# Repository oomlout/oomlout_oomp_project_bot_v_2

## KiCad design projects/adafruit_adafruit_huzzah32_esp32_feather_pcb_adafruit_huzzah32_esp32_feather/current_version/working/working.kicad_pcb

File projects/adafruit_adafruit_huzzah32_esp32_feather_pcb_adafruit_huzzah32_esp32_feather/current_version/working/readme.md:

# adafruit_huzzah32_esp32_feather_pcb
 
## summary 
* id: adafruit_adafruit_huzzah32_esp32_feather_pcb_adafruit_huzzah32_esp32_feather
* user: adafruit
* name: adafruit_huzzah32_esp32_feather_pcb
* board: adafruit_huzzah32_esp32_feather
* repo: https://github.com/adafruit/Adafruit-HUZZAH32-ESP32-Feather-PCB

* src_file_repo_sch: 
* src_file_repo_sch_link: https://github.com/adafruit/Adafruit-HUZZAH32-ESP32-Feather-PCB/tree/master/
* full details link: https://github.com/oomlout/oomlout_oomp_project_bot_v_2/tree/main/projects/adafruit_adafruit_huzzah32_esp32_feather_pcb_adafruit_huzzah32_esp32_feather/current_version/working  

## schematic  
  
[schematic (pdf)](working_schematic.pdf) 

## pcb  

[board (pdf)](working.pdf)  

## working_bom
| Id | Designator | Footprint | Quantity | Designation | Supplier and ref |  | None | 
| --- | --- | --- | --- | --- | --- | --- | --- | 
| 1 | @HOLE0,@HOLE1 |  | 2 |  |  |  | [''] | 
| 2 | C1,C2 | 0805-NO | 2 | 10uF |  |  | [''] | 
| 3 | U$35,U$34 | FIDUCIAL_1MM | 2 | FIDUCIAL_1MM |  |  | [''] | 
| 4 | U3 | SOT23-5 | 1 | MCP73831T-2ACI/OT |  |  | [''] | 
| 5 | R4 | 0603-NO | 1 | 4.7K |  |  | [''] | 
| 6 | SW2 | BTN_KMR2_4.6X2.8 | 1 | KMR2 |  |  | [''] | 
| 7 | C6,C8,C3 | 0805-NO | 3 | 10ÂµF |  |  | [''] | 
| 8 | R12,R3,R7,R1 | 0603-NO | 4 | 100K |  |  | [''] | 
| 9 | IC1 | QFN24_4MM_SMSC | 1 | CP2104 |  |  | [''] | 
| 10 | U$14 | ADAFRUIT_2.5MM | 1 |  |  |  | [''] | 
| 11 | X2 | WROOM32_SKINNY | 1 | ESP32_WROOM32_SKINNY |  |  | [''] | 
| 12 | C4,C7 | 0603-NO | 2 | 1uF |  |  | [''] | 
| 13 | JP1 | 1X16_ROUND_MIN | 1 |  |  |  | [''] | 
| 14 | R2,R10 | 0603-NO | 2 | 1K |  |  | [''] | 
| 15 | Q2,Q1 | SOT23-3 | 2 | mmbt2222 |  |  | [''] | 
| 16 | D4 | SOD-123 | 1 | MBR120 |  |  | [''] | 
| 17 | U$32,U$31 | MOUNTINGHOLE_2.5_PLATED | 2 | MOUNTINGHOLE2.5 |  |  | [''] | 
| 18 | X4 | 4UCONN_20329_V2 | 1 | 20329 |  |  | [''] | 
| 19 | CHG0 | CHIPLED_0805_NOOUTLINE | 1 | ORANGE |  |  | [''] | 
| 20 | R13 | RESPACK_4X0603 | 1 | 10K |  |  | [''] | 
| 21 | U2 | SOT23-5 | 1 | AP2112-3.3 |  |  | [''] | 
| 22 | Q3 | SOT23-R | 1 | DMG3415U |  |  | [''] | 
| 23 | D3 | CHIPLED_0805_NOOUTLINE | 1 | RED |  |  | [''] | 
| 24 | U$15 | ADAFRUIT_3.5MM | 1 |  |  |  | [''] | 
| 25 | JP3 | 1X12_ROUND_MIN | 1 |  |  |  | [''] | 
| 26 | X1 | JSTPH2 | 1 | JSTPH |  |  | [''] | 
| 27 | U$9 | FEATHERLOGO_MED | 1 |  |  |  | [''] | 
| 28 | U$43 | HUZZAH32 | 1 |  |  |  | [''] | 
| 29 | U$7 | ADAFRUIT_5MM | 1 |  |  |  | [''] | 
| 30 | U$13 | PCBFEAT-REV-040 | 1 |  |  |  | [''] | 

## bom_schematic
| Ref | Qnty | Value | Cmp name | Footprint | Description | Vendor | DNP | 
| --- | --- | --- | --- | --- | --- | --- | --- | 
| C1, C2 | 2 | 10uF | CAP_CERAMIC0805-NOOUTLINE | working:0805-NO |  |  |  | 
| C3, C6, C8 | 3 | 10ÂµF | CAP_CERAMIC0805-NOOUTLINE | working:0805-NO |  |  |  | 
| C4, C7 | 2 | 1uF | CAP_CERAMIC0603_NO | working:0603-NO |  |  |  | 
| CHG0 | 1 | ORANGE | LED0805_NOOUTLINE | working:CHIPLED_0805_NOOUTLINE |  |  |  | 
| D3 | 1 | RED | LED0805_NOOUTLINE | working:CHIPLED_0805_NOOUTLINE |  |  |  | 
| D4 | 1 | MBR120 | DIODE-SCHOTTKYSOD-123 | working:SOD-123 |  |  |  | 
| IC1 | 1 | CP2104 | CP2104 | working:QFN24_4MM_SMSC |  |  |  | 
| JP1 | 1 | HEADER-1X16_MIN | HEADER-1X16_MIN | working:1X16_ROUND_MIN |  |  |  | 
| JP3 | 1 | HEADER-1X12_MIN | HEADER-1X12_MIN | working:1X12_ROUND_MIN |  |  |  | 
| Q1, Q2 | 2 | mmbt2222 | TRANSISTOR_NPNSOT23-3 | working:SOT23-3 |  |  |  | 
| Q3 | 1 | DMG3415U | MOSFET-P | working:SOT23-R |  |  |  | 
| R1, R3, R7, R12 | 4 | 100K | RESISTOR_0603_NOOUT | working:0603-NO |  |  |  | 
| R2, R10 | 2 | 1K | RESISTOR_0603_NOOUT | working:0603-NO |  |  |  | 
| R4 | 1 | 4.7K | RESISTOR_0603_NOOUT | working:0603-NO |  |  |  | 
| R13 | 1 | 10K | RESISTOR_4PACK | working:RESPACK_4X0603 |  |  |  | 
| SW2 | 1 | KMR2 | SWITCH_TACT_SMT4.6X2.8 | working:BTN_KMR2_4.6X2.8 |  |  |  | 
| U2 | 1 | AP2112-3.3 | VREG_SOT23-5 | working:SOT23-5 |  |  |  | 
| U3 | 1 | MCP73831T-2ACI/OT | MCP73831/2 | working:SOT23-5 |  |  |  | 
| U$31, U$32 | 2 | MOUNTINGHOLE2.5 | MOUNTINGHOLE2.5 | working:MOUNTINGHOLE_2.5_PLATED |  |  |  | 
| U$34, U$35 | 2 | FIDUCIAL_1MM | FIDUCIAL_1MM | working:FIDUCIAL_1MM |  |  |  | 
| X1 | 1 | JSTPH | CON_JST_PH_2PIN | working:JSTPH2 |  |  |  | 
| X2 | 1 | ESP32_WROOM32_SKINNY | ESP32_WROOM32_SKINNY | working:WROOM32_SKINNY |  |  |  | 
| X4 | 1 | 20329 | USB_MICRO_20329_V2 | working:4UCONN_20329_V2 |  |  |  | 

## mounting_holes
| x | y | package | value | ref | size | 
| --- | --- | --- | --- | --- | --- | 
| 0.0 | 17.78 | MOUNTINGHOLE_2.5_PLATED | MOUNTINGHOLE2.5 | U$31 | m3 | 
| 0.0 | 0.0 | MOUNTINGHOLE_2.5_PLATED | MOUNTINGHOLE2.5 | U$32 | m3 |

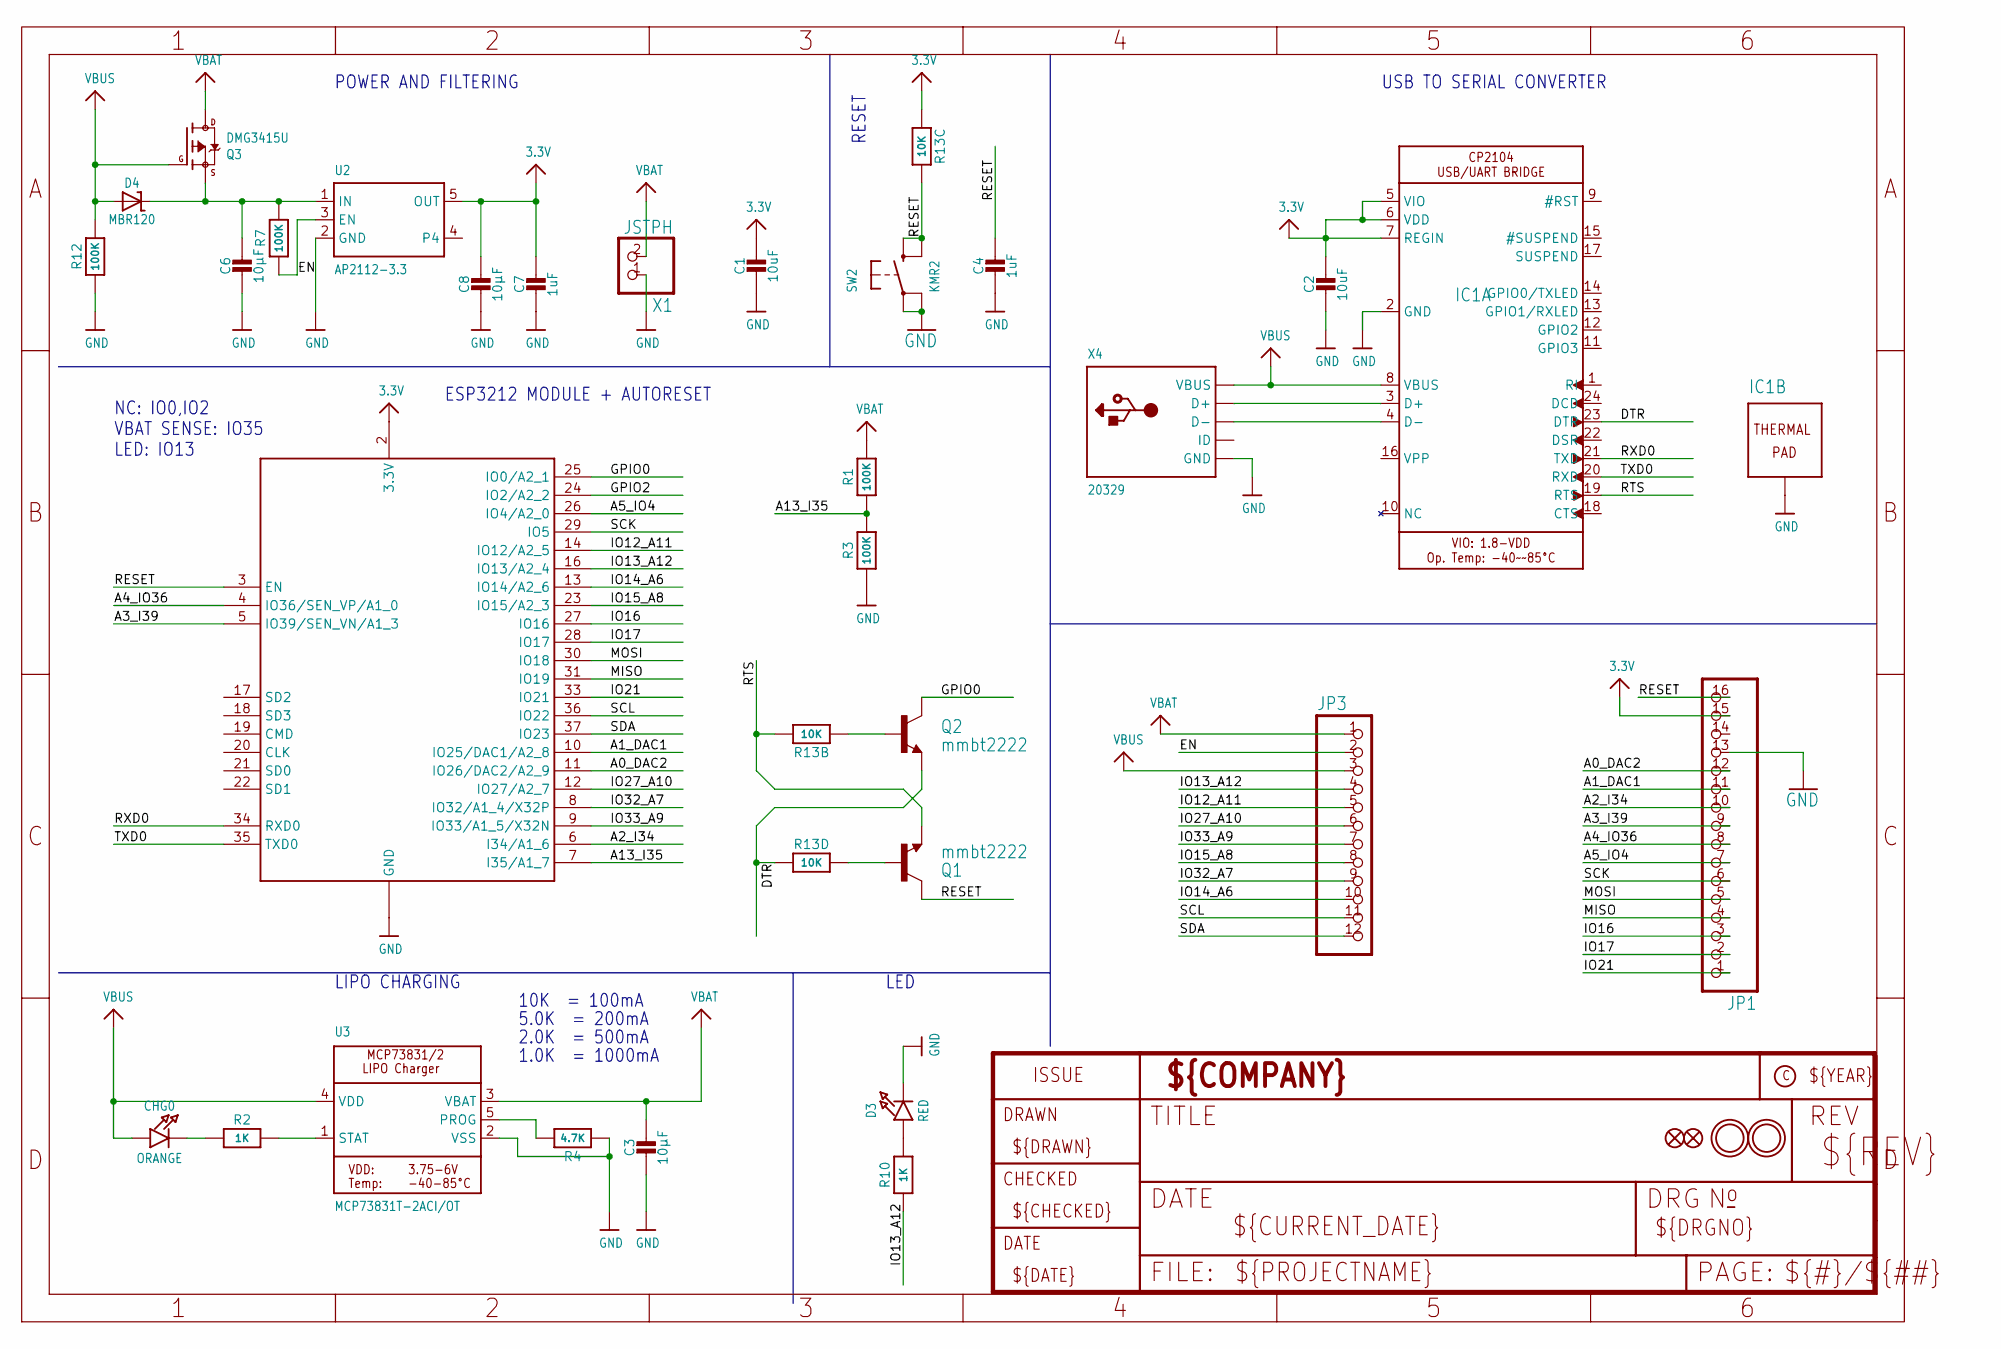
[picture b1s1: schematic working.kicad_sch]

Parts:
C1, C2: 10uF; 0805-NO
C3, C6, C8: 10µF; 0805-NO
C4, C7: 1uF; 0603-NO
CHG0: ORANGE; CHIPLED_0805_NOOUTLINE
D3: RED; CHIPLED_0805_NOOUTLINE
D4: MBR120; SOD-123
IC1: CP2104; QFN24_4MM_SMSC
JP1: HEADER-1X16_MIN; 1X16_ROUND_MIN
JP3: HEADER-1X12_MIN; 1X12_ROUND_MIN
Q1, Q2: mmbt2222; SOT23-3
Q3: DMG3415U; SOT23-R
R1, R3, R7, R12: 100K; 0603-NO
R2, R10: 1K; 0603-NO
R4: 4.7K; 0603-NO
R13: 10K; RESPACK_4X0603
SW2: KMR2; BTN_KMR2_4.6X2.8
U2: AP2112-3.3; SOT23-5
U3: MCP73831T-2ACI/OT; SOT23-5
U$31, U$32: MOUNTINGHOLE2.5; MOUNTINGHOLE_2.5_PLATED
U$34, U$35: FIDUCIAL_1MM
X1: JSTPH; JSTPH2
X2: ESP32_WROOM32_SKINNY; WROOM32_SKINNY
X4: 20329; 4UCONN_20329_V2

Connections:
3.3V: C1.1, C2.1, C7.1, C8.1, IC1.5 (VIO), IC1.6 (VDD), IC1.7 (REGIN), JP1.15, R13.3 (1), U2.5 (OUT), X2.2 (3.3V)
A0_DAC2: JP1.12, X2.11 (IO26/DAC2/A2_9)
A1_DAC1: JP1.11, X2.10 (IO25/DAC1/A2_8)
A2_I34: JP1.10, X2.6 (I34/A1_6)
A3_I39: JP1.9, X2.5 (IO39/SEN_VN/A1_3)
A4_IO36: JP1.8, X2.4 (IO36/SEN_VP/A1_0)
A5_IO4: JP1.7, X2.26 (IO4/A2_0)
A13_I35: R1.1, R3.2, X2.7 (I35/A1_7)
DTR: IC1.23 (DTR), Q2.2 (E), R13.4 (1)
EN: JP3.2, R7.1, U2.3 (EN)
GND: C1.2, C2.2, C3.2, C4.2, C6.2, C7.2, C8.2, D3.C, IC1.2 (GND), IC1.THERM (TP), JP1.13, R3.1, R4.1, R12.1, SW2.A, SW2.A' (P1), U2.2 (GND), U3.2 (VSS), X1.1, X2.1 (GND), X2.15 (GND), X2.38 (GND), X2.P$1 (GND), X4.BASE@1 (GND), X4.BASE@2 (GND), X4.GND, X4.SPRT@1 (GND), X4.SPRT@2 (GND), X4.SPRT@3 (GND), X4.SPRT@4 (GND)
GPIO0: Q2.3 (C), X2.25 (IO0/A2_1)
GPIO2: X2.24 (IO2/A2_2)
IO12_A11: JP3.5, X2.14 (IO12/A2_5)
IO13_A12: JP3.4, R10.1, X2.16 (IO13/A2_4)
IO14_A6: JP3.10, X2.13 (IO14/A2_6)
IO15_A8: JP3.8, X2.23 (IO15/A2_3)
IO16: JP1.3, X2.27 (IO16)
IO17: JP1.2, X2.28 (IO17)
IO21: JP1.1, X2.33 (IO21)
IO27_A10: JP3.6, X2.12 (IO27/A2_7)
IO32_A7: JP3.9, X2.8 (IO32/A1_4/X32P)
IO33_A9: JP3.7, X2.9 (IO33/A1_5/X32N)
MISO: JP1.4, X2.31 (IO19)
MOSI: JP1.5, X2.30 (IO18)
unnamed: CHG0.C, R2.1
unnamed: IC1.3 (D+), X4.D+
unnamed: R2.2, U3.1 (STAT)
unnamed: R4.2, U3.5 (PROG)
unnamed: D3.A, R10.2
unnamed: IC1.4 (D-), X4.D-
unnamed: C6.1, D4.C, Q3.2 (S), R7.2, U2.1 (IN)
unnamed: Q1.1 (B), R13.5 (2)
unnamed: Q2.1 (B), R13.2 (1)
RESET: C4.1, JP1.16, Q1.3 (C), R13.6 (2), SW2.B (S), SW2.B' (S1), X2.3 (EN)
RTS: IC1.19 (RTS), Q1.2 (E), R13.7 (2)
RXD0: IC1.21 (TXD), X2.34 (RXD0)
SCK: JP1.6, X2.29 (IO5)
SCL: JP3.11, X2.36 (IO22)
SDA: JP3.12, X2.37 (IO23)
TXD0: IC1.20 (RXD), X2.35 (TXD0)
VBAT: C3.1, JP3.1, Q3.3 (D), R1.2, U3.3 (VBAT), X1.2
VBUS: CHG0.A, D4.A, IC1.8 (VBUS), JP3.3, Q3.1 (G), R12.2, U3.4 (VDD), X4.VBUS

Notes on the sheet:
LED
POWER AND FILTERING
2.0K = 500mA
NC: IO0,IO2 VBAT SENSE: IO35 LED: IO13
RESET
ESP3212 MODULE + AUTORESET
5.0K = 200mA
10K = 100mA
USB TO SERIAL CONVERTER
1.0K = 1000mA
LIPO CHARGING

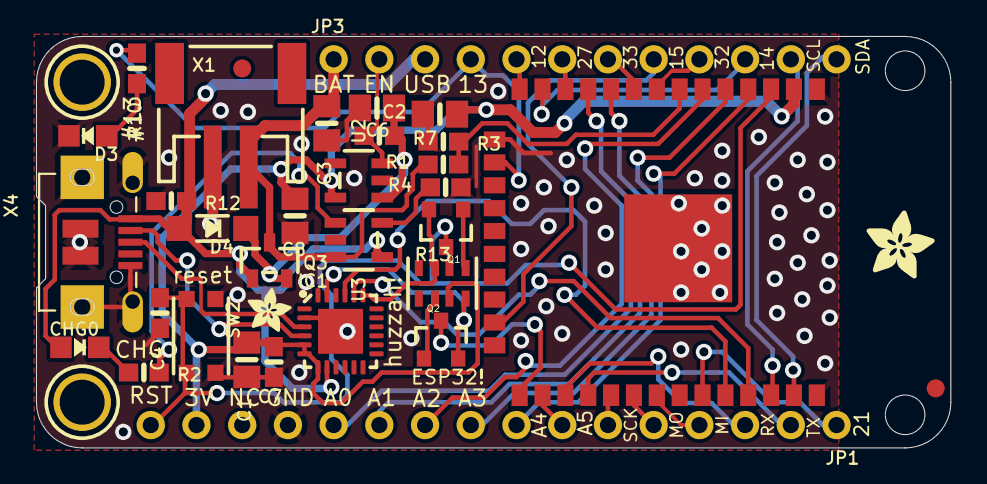
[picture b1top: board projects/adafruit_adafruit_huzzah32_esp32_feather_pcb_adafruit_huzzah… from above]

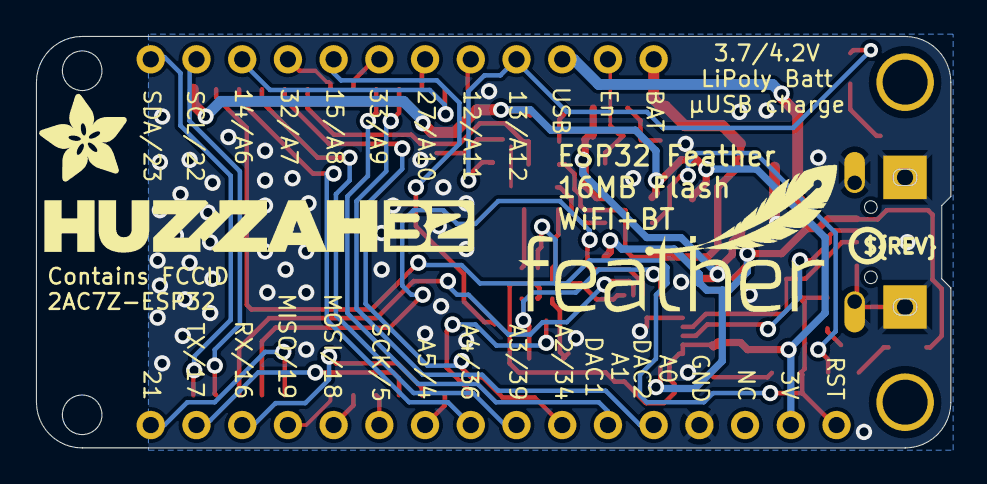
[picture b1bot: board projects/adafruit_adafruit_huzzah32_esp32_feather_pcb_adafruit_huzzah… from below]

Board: 2 copper layers, 50.8 x 22.9 mm, 42 parts (4 on the bottom side), 42 nets.

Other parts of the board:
@HOLE0, @HOLE1: (no value)
U$7: ADAFRUIT_5MM
U$9: FEATHERLOGO_MED
U$13: PCBFEAT-REV-040
U$14: ADAFRUIT_2.5MM
U$15: ADAFRUIT_3.5MM
U$43: HUZZAH32

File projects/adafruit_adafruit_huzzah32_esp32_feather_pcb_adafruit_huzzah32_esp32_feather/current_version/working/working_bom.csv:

"Id";"Designator";"Footprint";"Quantity";"Designation";"Supplier and ref";
1;"@HOLE0,@HOLE1";"";2;"";;;
2;"C1,C2";"0805-NO";2;"10uF";;;
3;"U$35,U$34";"FIDUCIAL_1MM";2;"FIDUCIAL_1MM";;;
4;"U3";"SOT23-5";1;"MCP73831T-2ACI/OT";;;
5;"R4";"0603-NO";1;"4.7K";;;
6;"SW2";"BTN_KMR2_4.6X2.8";1;"KMR2";;;
7;"C6,C8,C3";"0805-NO";3;"10µF";;;
8;"R12,R3,R7,R1";"0603-NO";4;"100K";;;
9;"IC1";"QFN24_4MM_SMSC";1;"CP2104";;;
10;"U$14";"ADAFRUIT_2.5MM";1;"";;;
11;"X2";"WROOM32_SKINNY";1;"ESP32_WROOM32_SKINNY";;;
12;"C4,C7";"0603-NO";2;"1uF";;;
13;"JP1";"1X16_ROUND_MIN";1;"";;;
14;"R2,R10";"0603-NO";2;"1K";;;
15;"Q2,Q1";"SOT23-3";2;"mmbt2222";;;
16;"D4";"SOD-123";1;"MBR120";;;
17;"U$32,U$31";"MOUNTINGHOLE_2.5_PLATED";2;"MOUNTINGHOLE2.5";;;
18;"X4";"4UCONN_20329_V2";1;"20329";;;
19;"CHG0";"CHIPLED_0805_NOOUTLINE";1;"ORANGE";;;
20;"R13";"RESPACK_4X0603";1;"10K";;;
21;"U2";"SOT23-5";1;"AP2112-3.3";;;
22;"Q3";"SOT23-R";1;"DMG3415U";;;
23;"D3";"CHIPLED_0805_NOOUTLINE";1;"RED";;;
24;"U$15";"ADAFRUIT_3.5MM";1;"";;;
25;"JP3";"1X12_ROUND_MIN";1;"";;;
26;"X1";"JSTPH2";1;"JSTPH";;;
27;"U$9";"FEATHERLOGO_MED";1;"";;;
28;"U$43";"HUZZAH32";1;"";;;
29;"U$7";"ADAFRUIT_5MM";1;"";;;
30;"U$13";"PCBFEAT-REV-040";1;"";;;

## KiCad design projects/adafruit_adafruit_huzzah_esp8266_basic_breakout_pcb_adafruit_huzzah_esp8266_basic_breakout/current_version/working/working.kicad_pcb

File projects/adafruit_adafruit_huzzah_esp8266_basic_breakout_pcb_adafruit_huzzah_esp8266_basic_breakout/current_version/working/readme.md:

# adafruit_huzzah_esp8266_basic_breakout_pcb
 
## summary 
* id: adafruit_adafruit_huzzah_esp8266_basic_breakout_pcb_adafruit_huzzah_esp8266_basic_breakout
* user: adafruit
* name: adafruit_huzzah_esp8266_basic_breakout_pcb
* board: adafruit_huzzah_esp8266_basic_breakout
* repo: https://github.com/adafruit/Adafruit-Huzzah-ESP8266-Basic-Breakout-PCB

* src_file_repo_sch: 
* src_file_repo_sch_link: https://github.com/adafruit/Adafruit-Huzzah-ESP8266-Basic-Breakout-PCB/tree/master/
* full details link: https://github.com/oomlout/oomlout_oomp_project_bot_v_2/tree/main/projects/adafruit_adafruit_huzzah_esp8266_basic_breakout_pcb_adafruit_huzzah_esp8266_basic_breakout/current_version/working  

## schematic  
  
[schematic (pdf)](working_schematic.pdf) 

## pcb  

[board (pdf)](working.pdf)  

## working_bom
| Id | Designator | Footprint | Quantity | Designation | Supplier and ref |  | None | 
| --- | --- | --- | --- | --- | --- | --- | --- | 
| 1 | JP4,JP5 | 1X10_ROUND70 | 2 |  |  |  | [''] | 
| 2 | C2,C1 | 0805-NO | 2 | 10uF |  |  | [''] | 
| 3 | X1 | ESP-12 | 1 | ESP-12 |  |  | [''] | 
| 4 | FID3,FID1 | FIDUCIAL_1MM | 2 | FIDUCIAL" |  |  | [''] | 
| 5 | D3 | CHIPLED_0805_NOOUTLINE | 1 | RED |  |  | [''] | 
| 6 | D6,D5 | SOD-123 | 2 | MBR120 |  |  | [''] | 
| 7 | R6,R1,R3,R7,R4 | 0805-NO | 5 | 10K |  |  | [''] | 
| 8 | U$16,U$15,U$17,U$18 | MOUNTINGHOLE_2.5_PLATED | 4 | MOUNTINGHOLE2.5 |  |  | [''] | 
| 9 | U1 | SOT23-5 | 1 | SPX3819 |  |  | [''] | 
| 10 | SW1,SW2 | BTN_KMR2_4.6X2.8 | 2 | KMR2 |  |  | [''] | 
| 11 | D2,D1 | SOD-323 | 2 | 1n4148 |  |  | [''] | 
| 12 | U$3 | ADAFRUIT_2.5MM | 1 |  |  |  | [''] | 
| 13 | R2 | 0805-NO | 1 | 1K |  |  | [''] | 
| 14 | JP1 | 1X06_ROUND_70 | 1 | FTDI |  |  | [''] | 
| 15 | U$12 | ADAFRUIT_TEXT_20MM | 1 |  |  |  | [''] | 
| 16 | U$2 | HUZZAHLOGO | 1 |  |  |  | [''] | 
| 17 | U$13 | PCBFEAT-REV-040 | 1 |  |  |  | [''] | 

## bom_schematic
| Ref | Qnty | Value | Cmp name | Footprint | Description | Vendor | DNP | 
| --- | --- | --- | --- | --- | --- | --- | --- | 
| C1, C2 | 2 | 10uF | CAP_CERAMIC0805-NOOUTLINE | working:0805-NO |  |  |  | 
| D1, D2 | 2 | 1n4148 | DIODESOD-323 | working:SOD-323 |  |  |  | 
| D3 | 1 | RED | LED0805_NOOUTLINE | working:CHIPLED_0805_NOOUTLINE |  |  |  | 
| D5, D6 | 2 | MBR120 | DIODE-SCHOTTKYSOD-123 | working:SOD-123 |  |  |  | 
| FID1, FID3 | 2 | FIDUCIAL"" | FIDUCIAL{dblquote}{dblquote} | working:FIDUCIAL_1MM |  |  |  | 
| JP1 | 1 | FTDI | HEADER-1X670MIL | working:1X06_ROUND_70 |  |  |  | 
| JP4, JP5 | 2 | HEADER-1X1070MIL | HEADER-1X1070MIL | working:1X10_ROUND70 |  |  |  | 
| R1, R3, R4, R6, R7 | 5 | 10K | RESISTOR0805_NOOUTLINE | working:0805-NO |  |  |  | 
| R2 | 1 | 1K | RESISTOR0805_NOOUTLINE | working:0805-NO |  |  |  | 
| SW1, SW2 | 2 | KMR2 | SWITCH_TACT_SMT4.6X2.8 | working:BTN_KMR2_4.6X2.8 |  |  |  | 
| U1 | 1 | SPX3819 | VREG_SOT23-5 | working:SOT23-5 |  |  |  | 
| U$15, U$16, U$17, U$18 | 4 | MOUNTINGHOLE2.5 | MOUNTINGHOLE2.5 | working:MOUNTINGHOLE_2.5_PLATED |  |  |  | 
| X1 | 1 | ESP-12 | ESP-12 | working:ESP-12 |  |  |  | 

## mounting_holes
| x | y | package | value | ref | size | 
| --- | --- | --- | --- | --- | --- | 
| 20.32 | 33.02 | MOUNTINGHOLE_2.5_PLATED | MOUNTINGHOLE2.5 | U$15 | m3 | 
| 0.0 | 33.02 | MOUNTINGHOLE_2.5_PLATED | MOUNTINGHOLE2.5 | U$16 | m3 | 
| 20.32 | 0.0 | MOUNTINGHOLE_2.5_PLATED | MOUNTINGHOLE2.5 | U$17 | m3 | 
| 0.0 | 0.0 | MOUNTINGHOLE_2.5_PLATED | MOUNTINGHOLE2.5 | U$18 | m3 |

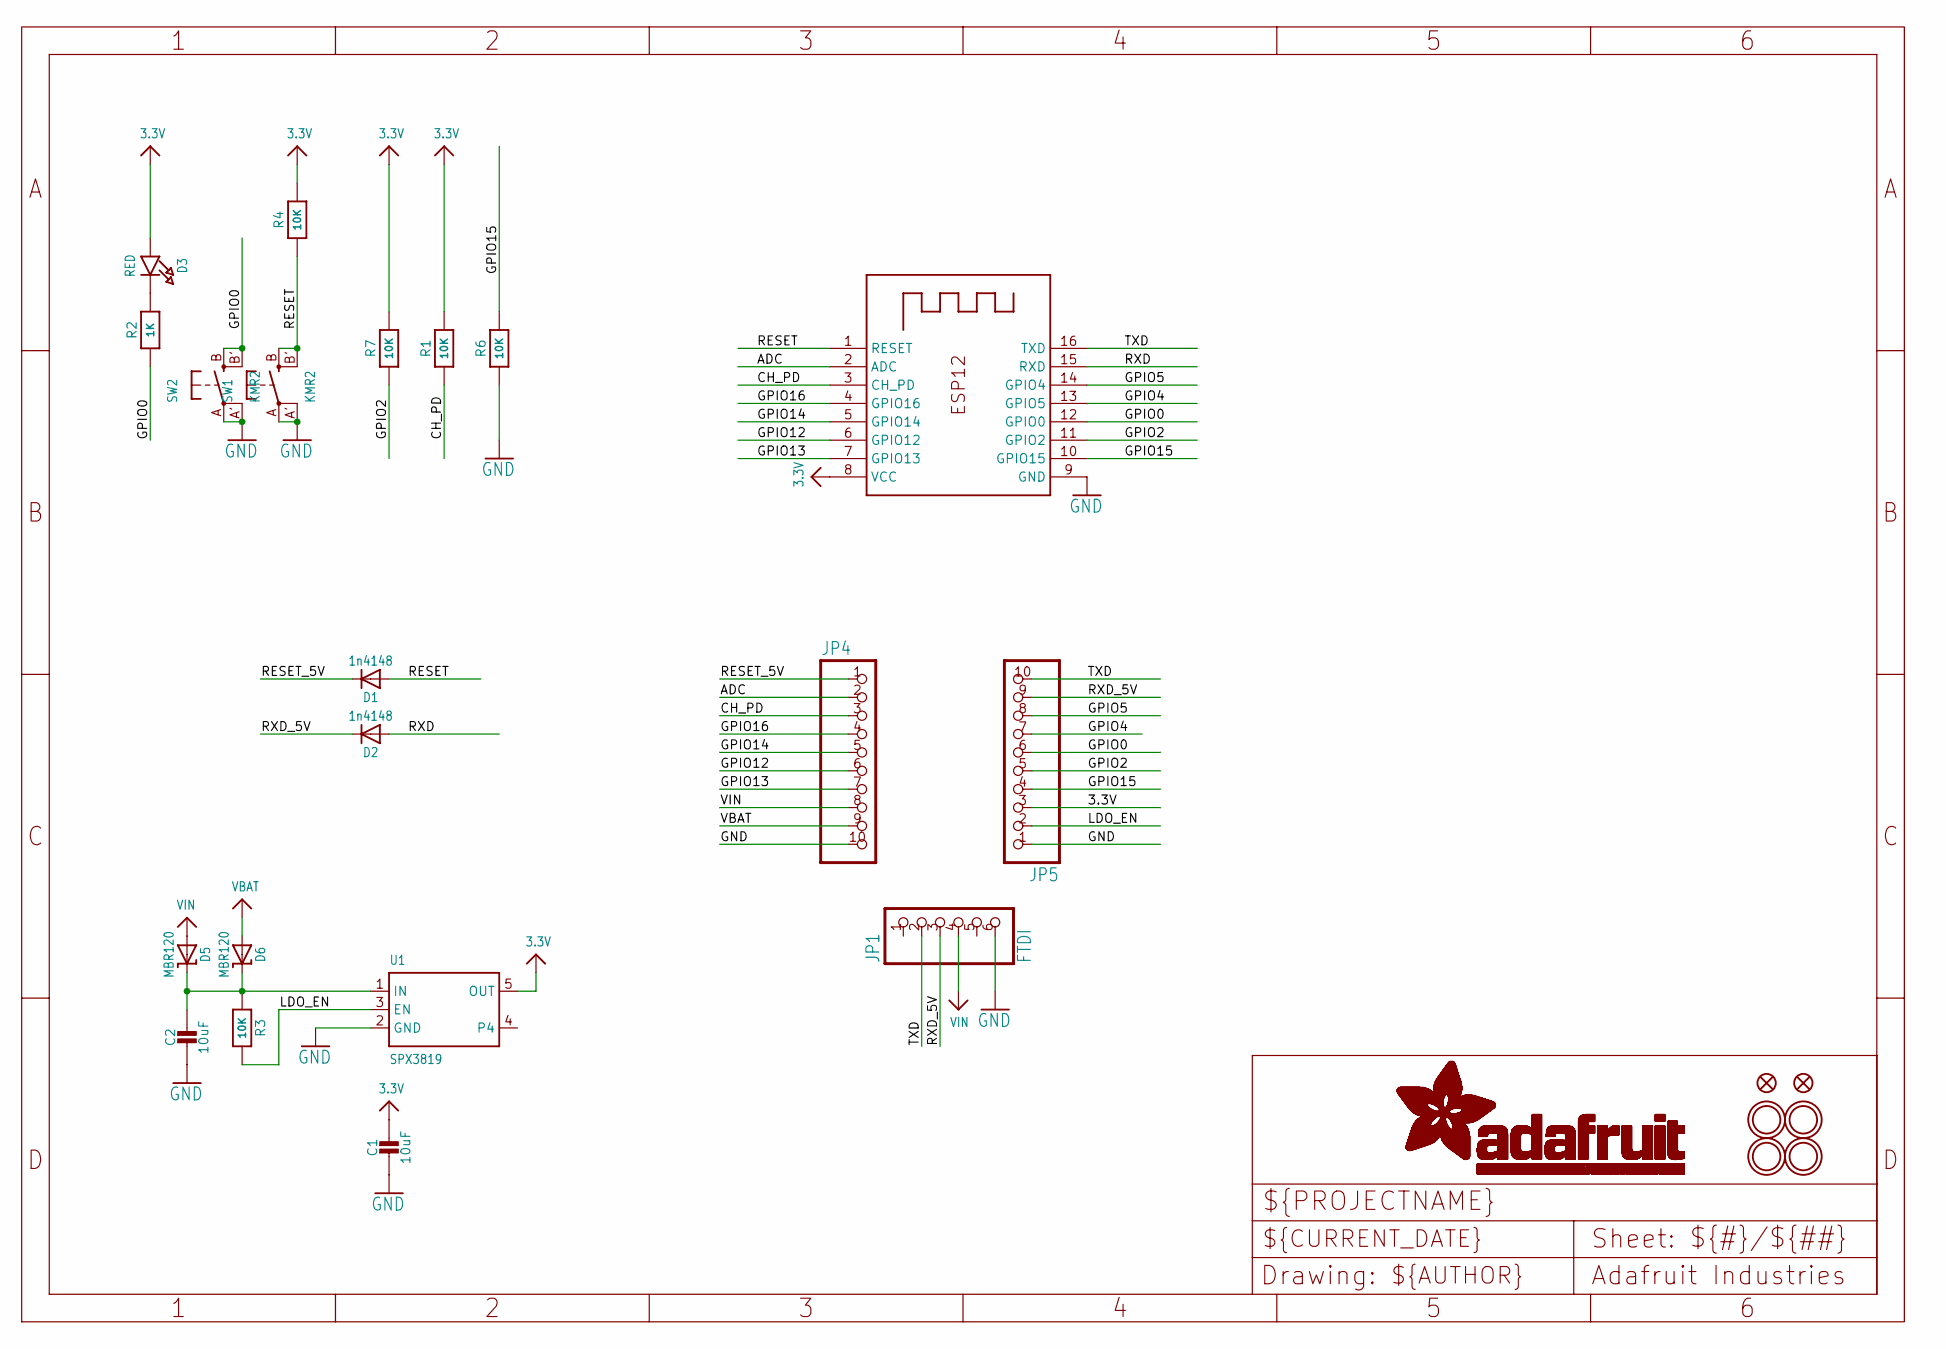
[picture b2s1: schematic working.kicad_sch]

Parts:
C1, C2: 10uF; 0805-NO
D1, D2: 1n4148; SOD-323
D3: RED; CHIPLED_0805_NOOUTLINE
D5, D6: MBR120; SOD-123
FID1, FID3: FIDUCIAL""; FIDUCIAL_1MM
JP1: FTDI; 1X06_ROUND_70
JP4, JP5: HEADER-1X1070MIL; 1X10_ROUND70
R1, R3, R4, R6, R7: 10K; 0805-NO
R2: 1K; 0805-NO
SW1, SW2: KMR2; BTN_KMR2_4.6X2.8
U1: SPX3819; SOT23-5
U$15, U$16, U$17, U$18: MOUNTINGHOLE2.5; MOUNTINGHOLE_2.5_PLATED
X1: ESP-12

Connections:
3.3V: C1.1, D3.A, JP5.3, R1.2, R4.2, R7.2, U1.5 (OUT), X1.8 (VCC)
ADC: JP4.2, X1.2 (ADC)
CH_PD: JP4.3, R1.1, X1.3 (CH_PD)
GND: C1.2, C2.2, JP1.6, JP4.10, JP5.1, R6.1, SW1.A, SW1.A' (P1), SW2.A, SW2.A' (P1), U1.2 (GND), X1.9 (GND)
GPIO0: JP5.6, R2.1, SW2.B (S), SW2.B' (S1), X1.12 (GPIO0)
GPIO2: JP5.5, R7.1, X1.11 (GPIO2)
GPIO4: JP5.7, X1.13 (GPIO5)
GPIO5: JP5.8, X1.14 (GPIO4)
GPIO12: JP4.6, X1.6 (GPIO12)
GPIO13: JP4.7, X1.7 (GPIO13)
GPIO14: JP4.5, X1.5 (GPIO14)
GPIO15: JP5.4, R6.2, X1.10 (GPIO15)
GPIO16: JP4.4, X1.4 (GPIO16)
LDO_EN: JP5.2, R3.2, U1.3 (EN)
unnamed: D3.C, R2.2
unnamed: C2.1, D5.C, D6.C, R3.1, U1.1 (IN)
RESET: D1.A, R4.1, SW1.B (S), SW1.B' (S1), X1.1 (RESET)
RESET_5V: D1.C, JP4.1
RXD: D2.A, X1.15 (RXD)
RXD_5V: D2.C, JP1.3, JP5.9
TXD: JP1.2, JP5.10, X1.16 (TXD)
VBAT: D6.A, JP4.9
VIN: D5.A, JP1.4, JP4.8

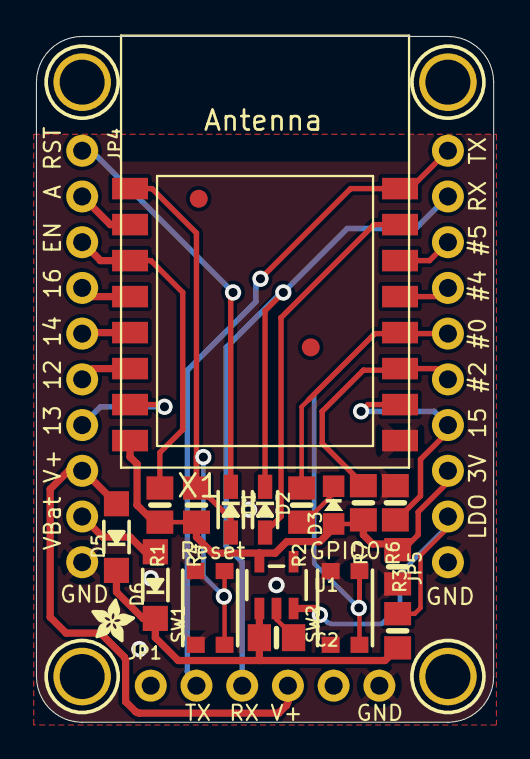
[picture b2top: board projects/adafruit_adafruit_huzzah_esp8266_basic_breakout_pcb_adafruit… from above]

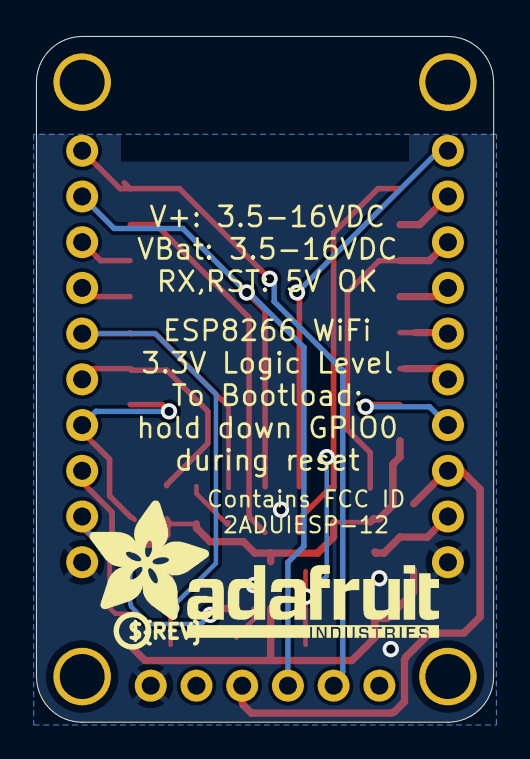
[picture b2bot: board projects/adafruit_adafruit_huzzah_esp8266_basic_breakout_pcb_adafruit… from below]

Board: 16 copper layers, 25.4 x 38.1 mm, 30 parts (3 on the bottom side), 23 nets.

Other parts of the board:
U$2: HUZZAHLOGO
U$3: ADAFRUIT_2.5MM
U$12: ADAFRUIT_TEXT_20MM
U$13: PCBFEAT-REV-040

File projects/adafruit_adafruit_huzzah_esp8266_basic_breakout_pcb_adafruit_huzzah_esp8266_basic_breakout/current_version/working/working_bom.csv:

"Id";"Designator";"Footprint";"Quantity";"Designation";"Supplier and ref";
1;"JP4,JP5";"1X10_ROUND70";2;"";;;
2;"C2,C1";"0805-NO";2;"10uF";;;
3;"X1";"ESP-12";1;"ESP-12";;;
4;"FID3,FID1";"FIDUCIAL_1MM";2;"FIDUCIAL""";;;
5;"D3";"CHIPLED_0805_NOOUTLINE";1;"RED";;;
6;"D6,D5";"SOD-123";2;"MBR120";;;
7;"R6,R1,R3,R7,R4";"0805-NO";5;"10K";;;
8;"U$16,U$15,U$17,U$18";"MOUNTINGHOLE_2.5_PLATED";4;"MOUNTINGHOLE2.5";;;
9;"U1";"SOT23-5";1;"SPX3819";;;
10;"SW1,SW2";"BTN_KMR2_4.6X2.8";2;"KMR2";;;
11;"D2,D1";"SOD-323";2;"1n4148";;;
12;"U$3";"ADAFRUIT_2.5MM";1;"";;;
13;"R2";"0805-NO";1;"1K";;;
14;"JP1";"1X06_ROUND_70";1;"FTDI";;;
15;"U$12";"ADAFRUIT_TEXT_20MM";1;"";;;
16;"U$2";"HUZZAHLOGO";1;"";;;
17;"U$13";"PCBFEAT-REV-040";1;"";;;

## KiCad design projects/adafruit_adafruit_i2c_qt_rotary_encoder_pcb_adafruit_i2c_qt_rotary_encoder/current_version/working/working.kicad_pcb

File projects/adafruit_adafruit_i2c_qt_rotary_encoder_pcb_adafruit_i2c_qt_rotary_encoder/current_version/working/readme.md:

# adafruit_i2c_qt_rotary_encoder_pcb
 
## summary 
* id: adafruit_adafruit_i2c_qt_rotary_encoder_pcb_adafruit_i2c_qt_rotary_encoder
* user: adafruit
* name: adafruit_i2c_qt_rotary_encoder_pcb
* board: adafruit_i2c_qt_rotary_encoder
* repo: https://github.com/adafruit/Adafruit-I2C-QT-Rotary-Encoder-PCB

* src_file_repo_sch: 
* src_file_repo_sch_link: https://github.com/adafruit/Adafruit-I2C-QT-Rotary-Encoder-PCB/tree/main/
* full details link: https://github.com/oomlout/oomlout_oomp_project_bot_v_2/tree/main/projects/adafruit_adafruit_i2c_qt_rotary_encoder_pcb_adafruit_i2c_qt_rotary_encoder/current_version/working  

## schematic  
  
[schematic (pdf)](working_schematic.pdf) 

## pcb  

[board (pdf)](working.pdf)  

## working_bom
| Id | Designator | Footprint | Quantity | Designation | Supplier and ref |  | None | 
| --- | --- | --- | --- | --- | --- | --- | --- | 
| 1 | JP2 | 1X06_ROUND_70 | 1 |  |  |  | [''] | 
| 2 | TP2,TP1,TP3 | TP15R | 3 | TPTP15R |  |  | [''] | 
| 3 | R7,R2,R1 | 0603-NO | 3 | 10K |  |  | [''] | 
| 4 | Q2 | SOT363 | 1 | BSS138 |  |  | [''] | 
| 5 | D1 | CHIPLED_0603_NOOUTLINE | 1 | GREEN |  |  | [''] | 
| 6 | U$29,U$25,U$30,U$27 | MOUNTINGHOLE_2.5_PLATED | 4 | MOUNTINGHOLE2.5 |  |  | [''] | 
| 7 | CONN3,CONN4 | JST_SH4 | 2 | STEMMA_I2C_QT |  |  | [''] | 
| 8 | FID4,FID3 | FIDUCIAL_1MM | 2 | FIDUCIAL_1MM |  |  | [''] | 
| 9 | U1 | SOT23-5 | 1 | AP2112K-3.3 |  |  | [''] | 
| 10 | IC1 | QFN24_4MM | 1 | ATSAMD09D14A-MU |  |  | [''] | 
| 11 | U$32 | ADAFRUIT_3.5MM | 1 |  |  |  | [''] | 
| 12 | SJ9,SJ8,SJ1 | SOLDERJUMPER_ARROW_NOPASTE | 3 |  |  |  | [''] | 
| 13 | C3,C2 | 0805-NO | 2 | 10uF |  |  | [''] | 
| 14 | C4 | 0603-NO | 1 | 0.1uF |  |  | [''] | 
| 15 | R6 | RESPACK_4X0603 | 1 | 10K |  |  | [''] | 
| 16 | D2 | CHIPLED_0603_NOOUTLINE | 1 | red |  |  | [''] | 
| 17 | U$33 | PCBFEAT-REV-040 | 1 |  |  |  | [''] | 
| 18 | U$35,U$34 | STEMMAQT | 2 |  |  |  | [''] | 
| 19 | LED1 | NEO3535_REVERSE | 1 | WS2812B_SK6812E |  |  | [''] | 
| 20 | SW1 | PEC11+SWITCH | 1 |  |  |  | [''] | 

## bom_schematic
| Ref | Qnty | Value | Cmp name | Footprint | Description | Vendor | DNP | 
| --- | --- | --- | --- | --- | --- | --- | --- | 
| C2, C3 | 2 | 10uF | CAP_CERAMIC0805-NOOUTLINE | working:0805-NO |  |  |  | 
| C4 | 1 | 0.1uF | CAP_CERAMIC0603_NO | working:0603-NO |  |  |  | 
| CONN3, CONN4 | 2 | STEMMA_I2C_QT | STEMMA_I2C_QT | working:JST_SH4 |  |  |  | 
| D1 | 1 | GREEN | LED0603_NOOUTLINE | working:CHIPLED_0603_NOOUTLINE |  |  |  | 
| D2 | 1 | red | LED0603_NOOUTLINE | working:CHIPLED_0603_NOOUTLINE |  |  |  | 
| FID3, FID4 | 2 | FIDUCIAL_1MM | FIDUCIAL_1MM | working:FIDUCIAL_1MM |  |  |  | 
| IC1 | 1 | ATSAMD09D14A-MU | ATSAMD09D14A-MU | working:QFN24_4MM |  |  |  | 
| JP2 | 1 | HEADER-1X670MIL | HEADER-1X670MIL | working:1X06_ROUND_70 |  |  |  | 
| LED1 | 1 | WS2812B_SK6812E | WS2812B_SK6812E | working:NEO3535_REVERSE |  |  |  | 
| Q2 | 1 | BSS138 | MOSFET-N_DUAL | working:SOT363 |  |  |  | 
| R1, R2, R7 | 3 | 10K | RESISTOR_0603_NOOUT | working:0603-NO |  |  |  | 
| R6 | 1 | 10K | RESISTOR_4PACK | working:RESPACK_4X0603 |  |  |  | 
| SJ1, SJ8, SJ9 | 3 | SOLDERJUMPER | SOLDERJUMPER | working:SOLDERJUMPER_ARROW_NOPASTE |  |  |  | 
| SW1 | 1 | ENCODER_PLUS_SWITCH_PEC11 | ENCODER_PLUS_SWITCH_PEC11 | working:PEC11+SWITCH |  |  |  | 
| TP1, TP2, TP3 | 3 | TPTP15R | TPTP15R | working:TP15R |  |  |  | 
| U1 | 1 | AP2112K-3.3 | VREG_SOT23-5 | working:SOT23-5 |  |  |  | 
| U$25, U$27, U$29, U$30 | 4 | MOUNTINGHOLE2.5 | MOUNTINGHOLE2.5 | working:MOUNTINGHOLE_2.5_PLATED |  |  |  | 

## mounting_holes
| x | y | package | value | ref | size | 
| --- | --- | --- | --- | --- | --- | 
| 0.0 | 20.32 | MOUNTINGHOLE_2.5_PLATED | MOUNTINGHOLE2.5 | U$25 | m3 | 
| 20.32 | 20.32 | MOUNTINGHOLE_2.5_PLATED | MOUNTINGHOLE2.5 | U$27 | m3 | 
| 0.0 | 0.0 | MOUNTINGHOLE_2.5_PLATED | MOUNTINGHOLE2.5 | U$29 | m3 | 
| 20.32 | 0.0 | MOUNTINGHOLE_2.5_PLATED | MOUNTINGHOLE2.5 | U$30 | m3 |

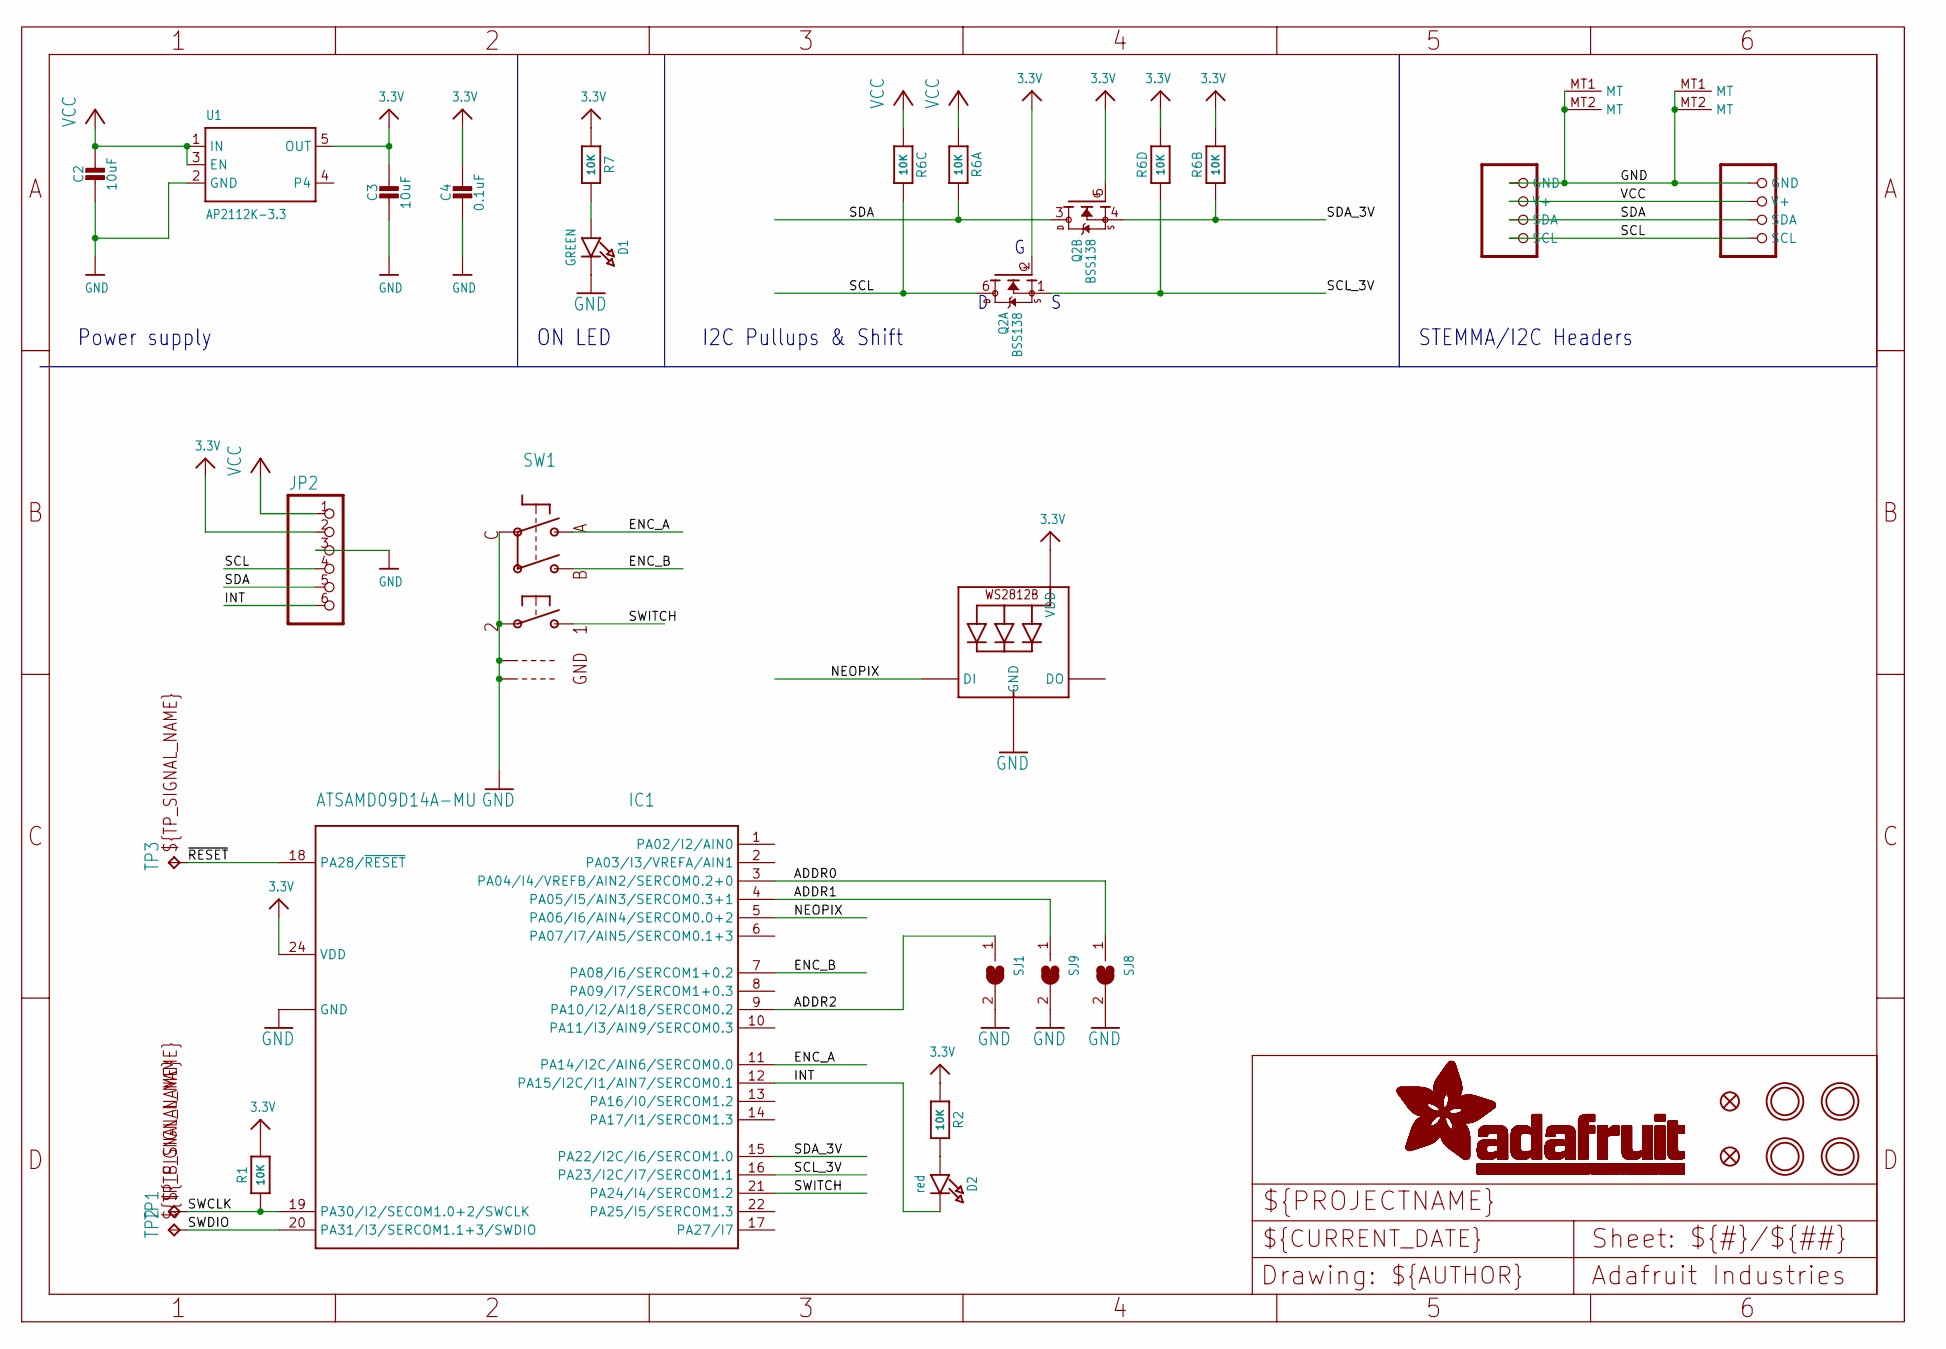
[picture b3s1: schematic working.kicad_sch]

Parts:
C2, C3: 10uF; 0805-NO
C4: 0.1uF; 0603-NO
CONN3, CONN4: STEMMA_I2C_QT; JST_SH4
D1: GREEN; CHIPLED_0603_NOOUTLINE
D2: red; CHIPLED_0603_NOOUTLINE
FID3, FID4: FIDUCIAL_1MM
IC1: ATSAMD09D14A-MU; QFN24_4MM
JP2: HEADER-1X670MIL; 1X06_ROUND_70
LED1: WS2812B_SK6812E; NEO3535_REVERSE
Q2: BSS138; SOT363
R1, R2, R7: 10K; 0603-NO
R6: 10K; RESPACK_4X0603
SJ1, SJ8, SJ9: SOLDERJUMPER; SOLDERJUMPER_ARROW_NOPASTE
SW1: ENCODER_PLUS_SWITCH_PEC11; PEC11+SWITCH
TP1, TP2, TP3: TPTP15R; TP15R
U1: AP2112K-3.3; SOT23-5
U$25, U$27, U$29, U$30: MOUNTINGHOLE2.5; MOUNTINGHOLE_2.5_PLATED

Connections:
3.3V: C3.1, C4.1, IC1.24 (VDD), JP2.2, LED1.1-VDD (VDD), Q2.2 (G), Q2.5 (G), R1.2, R2.1, R6.2 (1), R6.4 (1), R7.1, U1.5 (OUT)
ADDR0: IC1.3 (PA04/I4/VREFB/AIN2/SERCOM0.2+0), SJ8.1
ADDR1: IC1.4 (PA05/I5/AIN3/SERCOM0.3+1), SJ9.1
ADDR2: IC1.9 (PA10/I2/AI18/SERCOM0.2), SJ1.1
ENC_A: IC1.11 (PA14/I2C/AIN6/SERCOM0.0), SW1.P$A
ENC_B: IC1.7 (PA08/I6/SERCOM1+0.2), SW1.P$B
GND: C2.2, C3.2, C4.2, CONN3.1 (GND), CONN3.MT1 (MT), CONN3.MT2 (MT), CONN4.1 (GND), CONN4.MT1 (MT), CONN4.MT2 (MT), D1.C, IC1.23 (GND), IC1.THERM (GND), JP2.3, LED1.3-GND (GND), SJ1.2, SJ8.2, SJ9.2, SW1.P$2, SW1.P$C, SW1.P$GND1, SW1.P$GND2, U1.2 (GND)
INT: D2.C, IC1.12 (PA15/I2C/I1/AIN7/SERCOM0.1), JP2.6
unnamed: D1.A, R7.2
unnamed: D2.A, R2.2
NEOPIX: IC1.5 (PA06/I6/AIN4/SERCOM0.0+2), LED1.4-DIN (DI)
SCL: CONN3.4 (SCL), CONN4.4 (SCL), JP2.4, Q2.6 (D), R6.6 (2)
SCL_3V: IC1.16 (PA23/I2C/I7/SERCOM1.1), Q2.1 (S), R6.5 (2)
SDA: CONN3.3 (SDA), CONN4.3 (SDA), JP2.5, Q2.3 (D), R6.8 (2)
SDA_3V: IC1.15 (PA22/I2C/I6/SERCOM1.0), Q2.4 (S), R6.7 (2)
SWCLK: IC1.19 (PA30/I2/SECOM1.0+2/SWCLK), R1.1, TP1.TP
SWDIO: IC1.20 (PA31/I3/SERCOM1.1+3/SWDIO), TP2.TP
SWITCH: IC1.21 (PA24/I4/SERCOM1.2), SW1.P$1
VCC: C2.1, CONN3.2 (V+), CONN4.2 (V+), JP2.1, R6.1, R6.3 (1), U1.1 (IN), U1.3 (EN)
~RESET: IC1.18 (PA28/~RESET), TP3.TP

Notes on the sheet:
I2C Pullups & Shift
STEMMA/I2C Headers
Power supply
ON LED

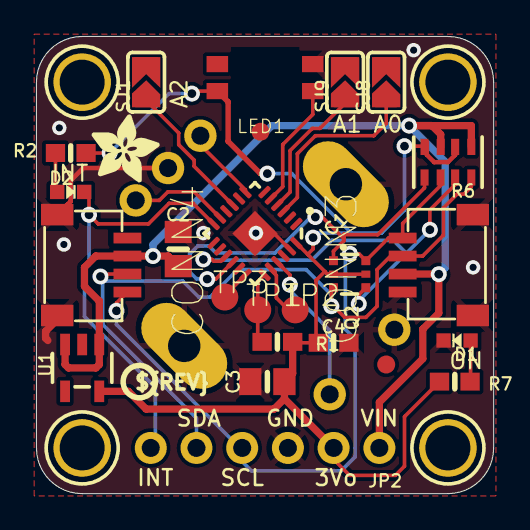
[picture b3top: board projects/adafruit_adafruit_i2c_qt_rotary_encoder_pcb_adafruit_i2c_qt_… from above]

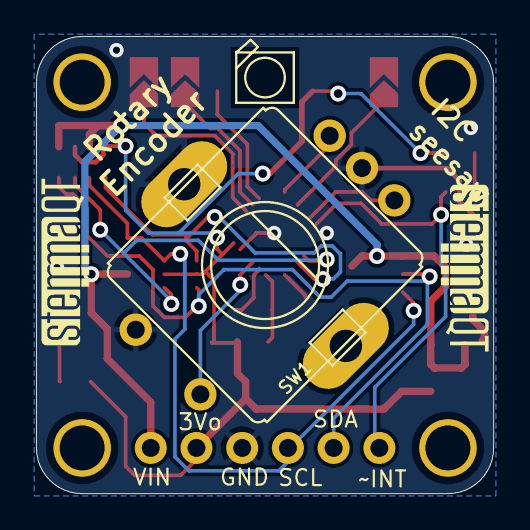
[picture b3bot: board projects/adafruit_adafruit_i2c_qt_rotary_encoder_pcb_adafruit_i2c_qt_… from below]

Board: 2 copper layers, 25.4 x 25.4 mm, 33 parts (4 on the bottom side), 20 nets.

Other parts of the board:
U$32: ADAFRUIT_3.5MM
U$33: PCBFEAT-REV-040
U$34, U$35: STEMMAQT

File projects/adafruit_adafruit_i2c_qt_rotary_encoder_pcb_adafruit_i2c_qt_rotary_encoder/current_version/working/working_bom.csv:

"Id";"Designator";"Footprint";"Quantity";"Designation";"Supplier and ref";
1;"JP2";"1X06_ROUND_70";1;"";;;
2;"TP2,TP1,TP3";"TP15R";3;"TPTP15R";;;
3;"R7,R2,R1";"0603-NO";3;"10K";;;
4;"Q2";"SOT363";1;"BSS138";;;
5;"D1";"CHIPLED_0603_NOOUTLINE";1;"GREEN";;;
6;"U$29,U$25,U$30,U$27";"MOUNTINGHOLE_2.5_PLATED";4;"MOUNTINGHOLE2.5";;;
7;"CONN3,CONN4";"JST_SH4";2;"STEMMA_I2C_QT";;;
8;"FID4,FID3";"FIDUCIAL_1MM";2;"FIDUCIAL_1MM";;;
9;"U1";"SOT23-5";1;"AP2112K-3.3";;;
10;"IC1";"QFN24_4MM";1;"ATSAMD09D14A-MU";;;
11;"U$32";"ADAFRUIT_3.5MM";1;"";;;
12;"SJ9,SJ8,SJ1";"SOLDERJUMPER_ARROW_NOPASTE";3;"";;;
13;"C3,C2";"0805-NO";2;"10uF";;;
14;"C4";"0603-NO";1;"0.1uF";;;
15;"R6";"RESPACK_4X0603";1;"10K";;;
16;"D2";"CHIPLED_0603_NOOUTLINE";1;"red";;;
17;"U$33";"PCBFEAT-REV-040";1;"";;;
18;"U$35,U$34";"STEMMAQT";2;"";;;
19;"LED1";"NEO3535_REVERSE";1;"WS2812B_SK6812E";;;
20;"SW1";"PEC11+SWITCH";1;"";;;
